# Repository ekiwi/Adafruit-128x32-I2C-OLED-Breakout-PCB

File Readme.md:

# SSD1306 Breakout

This is a cheap breakoutboard for a SSD1306 based OLED Display.

The footprint for the diplay is from the
`Adafruit 128x32 I2C OLED breakout board`.
Checkout their products if you want a well tested and presoldered
OLED breakoutboard.

Display footprint and original schematic designed by Adafruit Industries.  
Altered schmematic and board layout by eKiwi.  
Creative Commons Attribution, Share-Alike license, check license.txt for more information
All text above must be included in any redistribution

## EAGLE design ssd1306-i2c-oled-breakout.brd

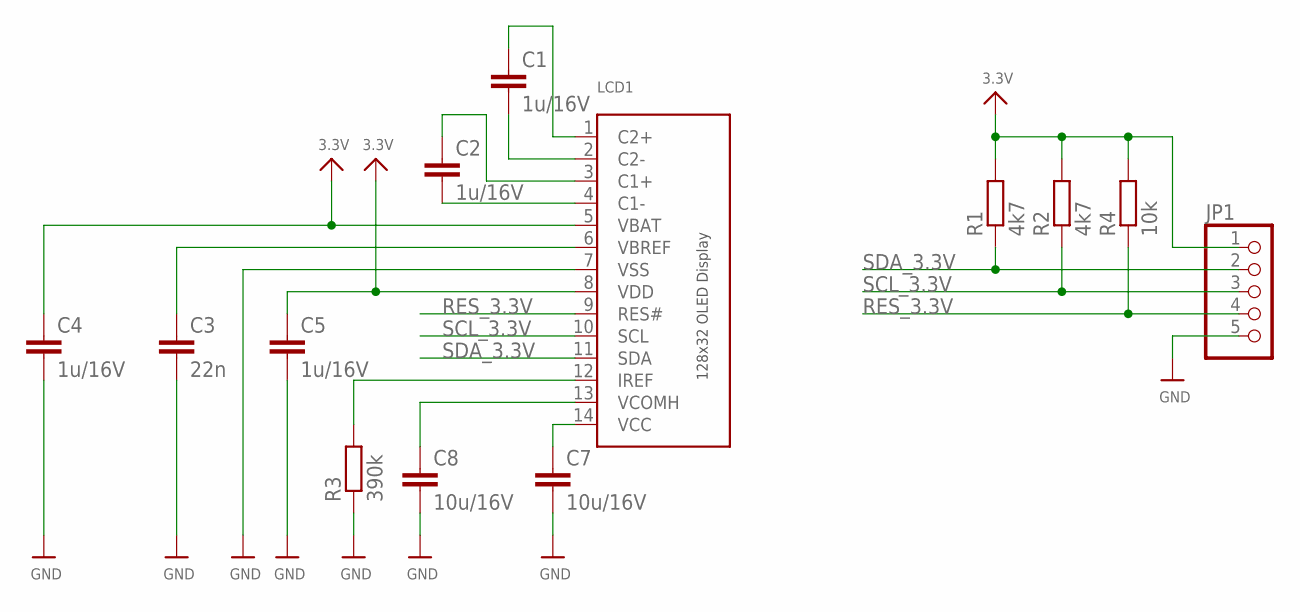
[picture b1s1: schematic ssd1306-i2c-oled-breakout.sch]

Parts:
C1, C2, C4, C5: 1u/16V; C0603
C3: 22n; C0603
C7, C8: 10u/16V; C0805
JP1: PINHD-1X5; 1X05
LCD1: DISP_OLED_UG-2832HSWEG02; UG-2832HSWEG02_WRAPUNDER
R1, R2: 4k7; R0805
R3: 390k; R0603
R4: 10k; R0805

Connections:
3.3V: C4.1, C5.1, JP1.1, LCD1.5 (VBAT), LCD1.8 (VDD), R1.2, R2.2, R4.2
GND: C3.2, C4.2, C5.2, C7.2, C8.2, JP1.5, LCD1.7 (VSS), R3.1
unnamed: C2.2, LCD1.4 (C1-)
unnamed: C2.1, LCD1.3 (C1+)
unnamed: C1.2, LCD1.2 (C2-)
unnamed: C1.1, LCD1.1 (C2+)
unnamed: C7.1, LCD1.14 (VCC)
unnamed: C8.1, LCD1.13 (VCOMH)
unnamed: LCD1.12 (IREF), R3.2
unnamed: C3.1, LCD1.6 (VBREF)
RES_3.3V: JP1.4, LCD1.9 (RES#), R4.1
SCL_3.3V: JP1.3, LCD1.10 (SCL), R2.1
SDA_3.3V: JP1.2, LCD1.11 (SDA), R1.1

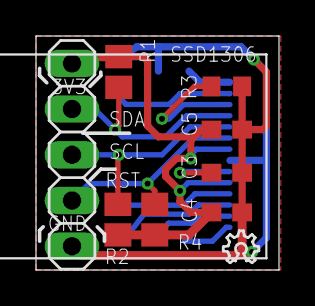
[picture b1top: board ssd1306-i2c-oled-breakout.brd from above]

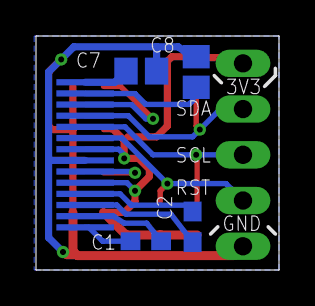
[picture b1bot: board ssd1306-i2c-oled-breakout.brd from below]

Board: 2 copper layers, 13.5 x 13.0 mm, 14 parts (4 on the bottom side), 13 nets.

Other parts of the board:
U$12: OSHW_6X70_NOTEXT

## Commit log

2014-06-21 Remove board layout. Alter schematic.
2014-06-21 Change Readme to reflect my changes.
2014-06-22 Completely new board layout.
